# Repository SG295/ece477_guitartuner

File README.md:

# Automatic Guitar Tuner 🎸
☆ **Automatic Guitar Tuner Project for ECE477 (Senior Design) @ Purdue University** ☆

**Team Page: https://engineering.purdue.edu/477grp11/Team/team.html**

**Project Description:** Our automatic guitar tuner is a tool anyone can use by selecting the desired note and holding the tool against the tuning peg. A microphone will listen as the string is plucked by the user and make the proper adjustments thorugh a motor. An LCD screen will communicate when the guitar adjustments are finished being made. The design will also have other modes such as a free spin mode to allow the motor to assist in the restringing of a guitar.
Design parameters are:
  * A 3D printed case that holds all the components (PCB, battery, motor, etc.)
  * An STM32 microcontroller that controls all the components of the tuner (battery, motor, LCD screen, microphone)
  * A stepper motor connected to the microcontroller that rotates based on feedback from the microphone
  * A digital microphone that listens when prompted by the microcontroller. First, I2S is used to read the digital signal and then DSP is performed so that the microcontroller knows what frequency is being played.
  * A rechargable battery connected to a battery management system and the microcontroller. Powers all the components in the tuner.
  * A graphical LCD screen that is controlled by buttons on the tuner. It includes "Power", "^", ">", "<", and "v" buttons for the user to press to control the contents of the screen.

***

**For team members:**

Please make a branch for your respective part and title it according (i.e. if you're working on the motor, you can just title it "motor").

The command to create a branch (do this locally after you've pulled):
  * git checkout -b NEW_BRANCH_NAME

The commands (in order) to push your NEW branch: 
  * git add .
  * git commit -m "put message here"
  * git push origin -u NEW_BRANCH_NAME
   
**Once you have created and pushed the branch, you can push normally if you're on the branch. You can check this with "git branch".**

I have setup a platoform IO project here with basic settings with the STM32F407VG Discovery Boards we have at our table (looks like the image below). Make sure you're actually within the project folder (titled "PlatformIO-GuitarTuner") and not this repo when trying to upload code to the board. I'll list some documentation that will be useful below:
  * Reference Manual: https://www.st.com/resource/en/reference_manual/dm00031020-stm32f405-415-stm32f407-417-stm32f427-437-and-stm32f429-439-advanced-arm-based-32-bit-mcus-stmicroelectronics.pdf
  * STM32F407 Data Sheet: https://www.st.com/resource/en/datasheet/dm00037051.pdf

**DISCOVERY BOARD:**

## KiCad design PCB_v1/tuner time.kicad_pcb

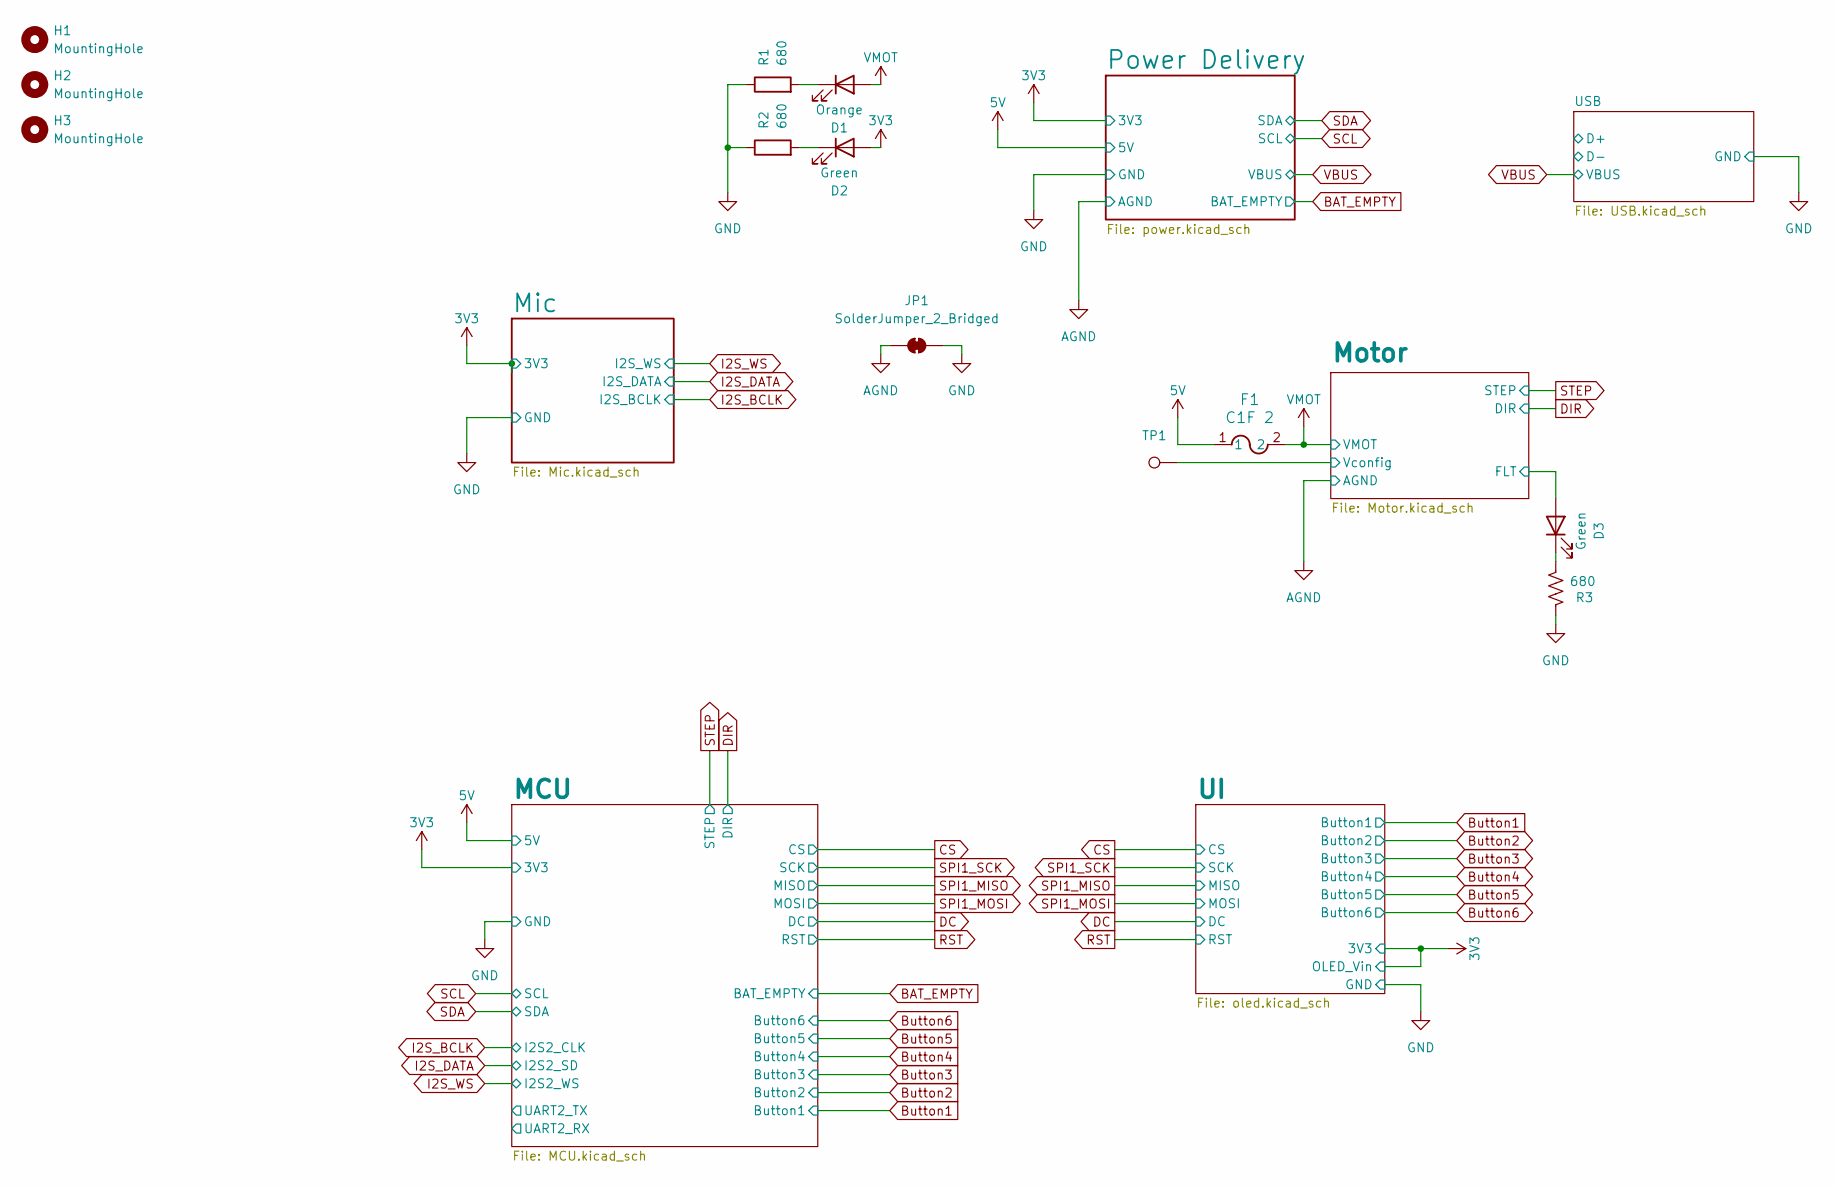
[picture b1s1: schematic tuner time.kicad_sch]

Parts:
D1: Orange; LED_0805_2012Metric_Pad1.15x1.40mm_HandSolder
D2, D3: Green; LED_0805_2012Metric_Pad1.15x1.40mm_HandSolder
F1: C1F 2; C1_BEL
H1, H2, H3: MountingHole; MountingHole_2.2mm_M2_DIN965_Pad_TopOnly
JP1: SolderJumper_2_Bridged; SolderJumper-2_P1.3mm_Bridged2Bar_RoundedPad1.0x1.5mm
R1, R2, R3: 680; R_0805_2012Metric
TP1: TestPoint_THTPad_D0.8mm_Drill0.4mm

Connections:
3V3: D2.2 (A); also elsewhere on the board
5V: F1.1; also elsewhere on the board
/Motor/FLT: D3.2 (A); also elsewhere on the board
/Motor/Vconfig: TP1.1; also elsewhere on the board
AGND: JP1.1 (A); also elsewhere on the board
GND: JP1.2 (B), R1.1, R2.1, R3.2; also elsewhere on the board
unnamed: D1.1 (K), R1.2
unnamed: D2.1 (K), R2.2
unnamed: D3.1 (K), R3.1
VMOT: D1.2 (A), F1.2; also elsewhere on the board

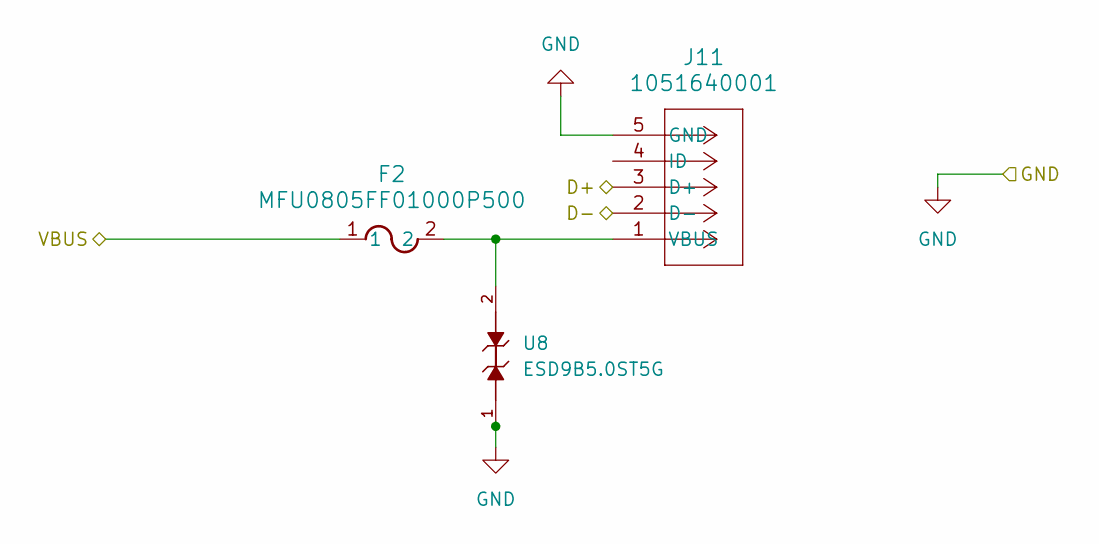
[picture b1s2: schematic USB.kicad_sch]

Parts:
F2: MFU0805FF01000P500; FUS_VISHAY_MFU0805_VIS
J11: 1051640001; CON00906_5_MOL
U8: ESD9B5.0ST5G; SODFL1006X40N

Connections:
GND: J11.5 (GND), U8.1; also elsewhere on the board
unnamed: F2.2, J11.1 (VBUS), U8.2
VBUS: F2.1; also elsewhere on the board

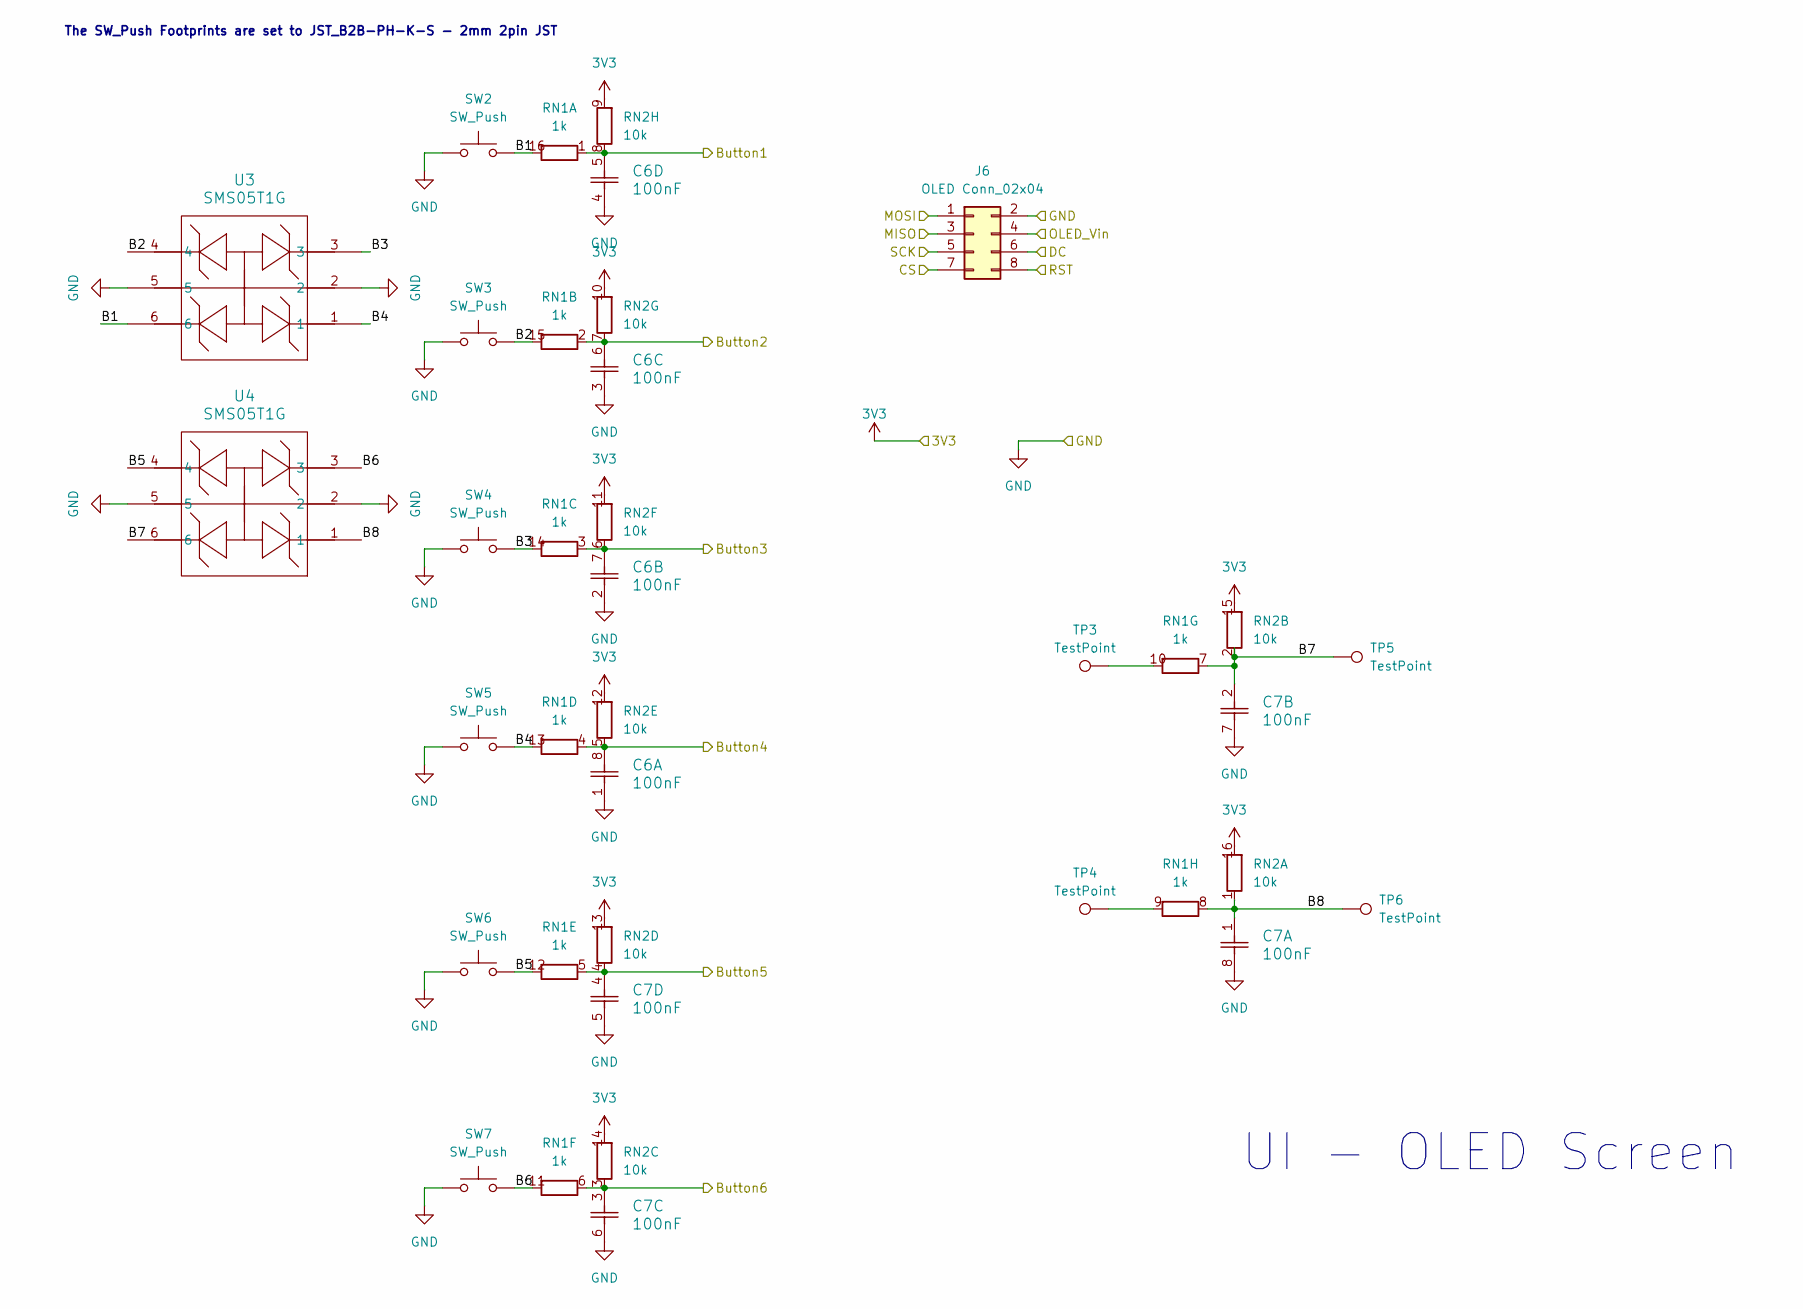
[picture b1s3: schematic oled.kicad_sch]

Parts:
C6, C7: 100nF; CAP_CA0612_3P2X1P6_YAG
J6: OLED Conn_02x04; PinHeader_2x04_P2.54mm_Vertical
RN1: 1k; RESCAXE50P280X160X55-16N
RN2: 10k; RESCAXE50P280X160X55-16N
SW2, SW3, SW4, SW5, SW6, SW7: SW_Push; JST_B2B-PH-K-S
TP3, TP4, TP5, TP6: TestPoint; TestPoint_THTPad_D0.8mm_Drill0.4mm
U3, U4: SMS05T1G; SOIC_05T1G_ONS

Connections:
3V3: J6.4, RN2.9 (R8.2), RN2.10 (R7.2), RN2.11 (R6.2), RN2.12 (R5.2), RN2.13 (R4.2), RN2.14 (R3.2), RN2.15 (R2.2), RN2.16 (R1.2); also elsewhere on the board
/UI/B1: RN1.16 (R1.2), SW2.2, U3.6
/UI/B2: RN1.15 (R2.2), SW3.2, U3.4
/UI/B3: RN1.14 (R3.2), SW4.2, U3.3
/UI/B4: RN1.13 (R4.2), SW5.2, U3.1
/UI/B5: RN1.12 (R5.2), SW6.2, U4.4
/UI/B6: RN1.11 (R6.2), SW7.2, U4.3
/UI/B7: C7.2, RN1.7 (R7.1), RN2.2 (R2.1), TP5.1, U4.6
/UI/B8: C7.1, RN1.8 (R8.1), RN2.1 (R1.1), TP6.1, U4.1
Button1: C6.5, RN1.1 (R1.1), RN2.8 (R8.1); also elsewhere on the board
Button2: C6.6, RN1.2 (R2.1), RN2.7 (R7.1); also elsewhere on the board
Button3: C6.7, RN1.3 (R3.1), RN2.6 (R6.1); also elsewhere on the board
Button4: C6.8, RN1.4 (R4.1), RN2.5 (R5.1); also elsewhere on the board
Button5: C7.4, RN1.5 (R5.1), RN2.4 (R4.1); also elsewhere on the board
Button6: C7.3, RN1.6 (R6.1), RN2.3 (R3.1); also elsewhere on the board
CS: J6.8; also elsewhere on the board
DC: J6.6; also elsewhere on the board
GND: C6.1, C6.2, C6.3, C6.4, C7.5, C7.6, C7.7, C7.8, J6.2, SW2.1, SW3.1, SW4.1, SW5.1, SW6.1, SW7.1, U3.2, U3.5, U4.2, U4.5; also elsewhere on the board
unnamed: RN1.10 (R7.2), TP3.1
unnamed: RN1.9 (R8.2), TP4.1
RST: J6.7; also elsewhere on the board
SPI1_MISO: J6.3; also elsewhere on the board
SPI1_MOSI: J6.1; also elsewhere on the board
SPI1_SCK: J6.5; also elsewhere on the board

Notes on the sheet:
The SW_Push Footprints are set to JST_B2B-PH-K-S - 2mm 2pin JST
UI - OLED Screen

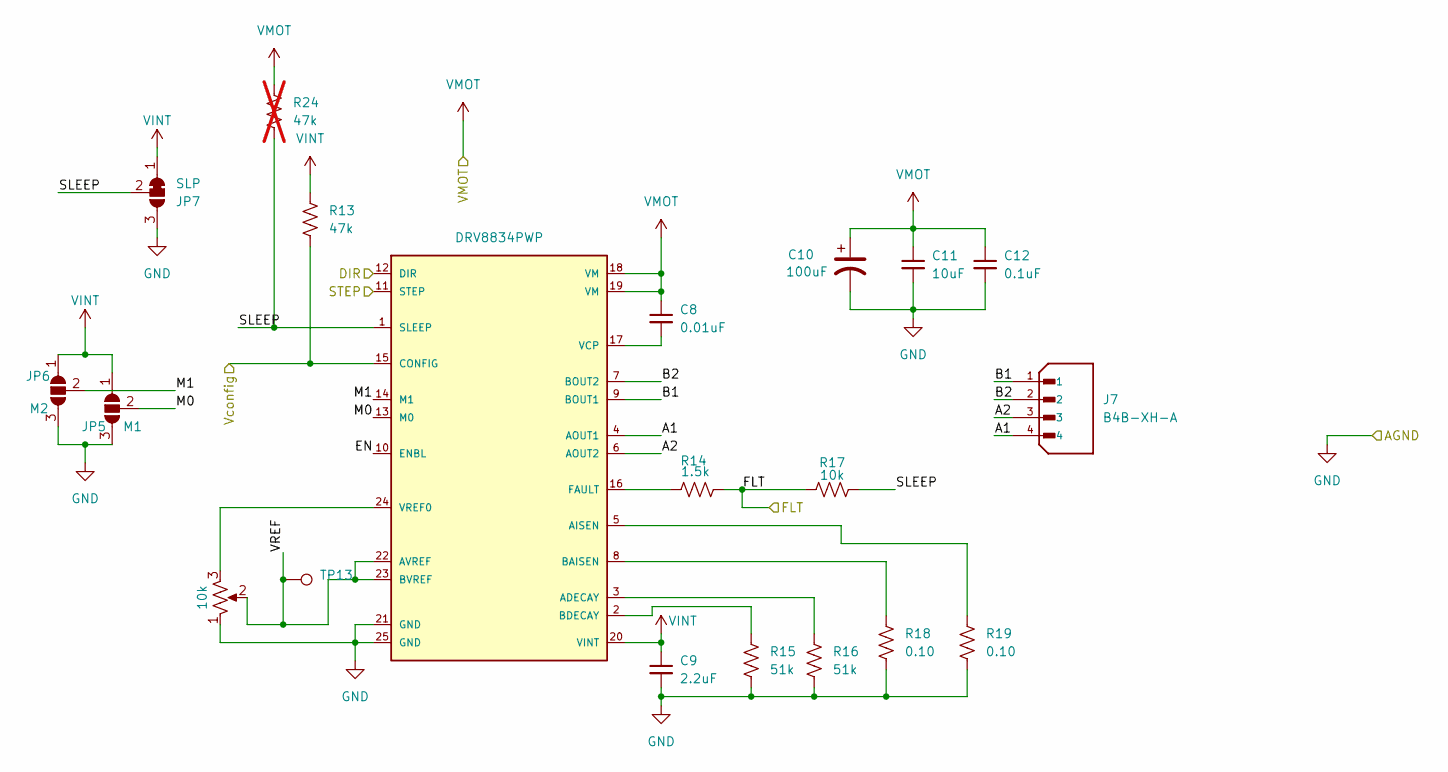
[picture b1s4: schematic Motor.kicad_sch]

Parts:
C8: 0.01uF; C_0805_2012Metric
C9: 2.2uF; C_0805_2012Metric
C10: 100uF; CAP_EEE1AA101WR
C11: 10uF; C_0805_2012Metric
C12: 0.1uF; C_0805_2012Metric
J7: B4B-XH-A; JST_B4B-XH-A; PARTREV 7/4/21
JP5: M1; SolderJumper-3_P1.3mm_Open_RoundedPad1.0x1.5mm
JP6: M2; SolderJumper-3_P1.3mm_Open_RoundedPad1.0x1.5mm
JP7: SLP; SolderJumper-3_P1.3mm_Bridged12_RoundedPad1.0x1.5mm
R13: 47k; R_0805_2012Metric
R14: 1.5k; R_0805_2012Metric
R15, R16: 51k; R_0805_2012Metric
R17: 10k; R_0805_2012Metric
R18, R19: 0.10; R_0805_2012Metric
R24: 47k; R_0805_2012Metric; not fitted
RV1: 10k; TRIM_TC33X-2-103E
TP13: TestPoint_THTPad_D0.8mm_Drill0.4mm
U5: DRV8834PWP; SOP65P640X120-25N

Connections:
/Motor/A1: J7.4, U5.4 (AOUT1)
/Motor/A2: J7.3, U5.6 (AOUT2)
/Motor/B1: J7.1, U5.9 (BOUT1)
/Motor/B2: J7.2, U5.7 (BOUT2)
/Motor/EN: U5.10 (ENBL)
/Motor/FLT: R14.2, R17.1; also elsewhere on the board
/Motor/M0: JP5.2 (C), U5.13 (M0)
/Motor/M1: JP6.2 (C), U5.14 (M1)
/Motor/SLEEP: JP7.2 (C), R17.2, R24.2, U5.1 (SLEEP)
/Motor/VREF: RV1.2, TP13.1, U5.22 (AVREF), U5.23 (BVREF)
/Motor/Vconfig: R13.2, U5.15 (CONFIG); also elsewhere on the board
AGND: C9.2, C10.2, C11.2, C12.2, JP5.3 (B), JP6.3 (B), JP7.3 (B), R15.2, R16.2, R18.2, R19.2, RV1.1, U5.21 (GND), U5.25 (GND); also elsewhere on the board
DIR: U5.12 (DIR); also elsewhere on the board
unnamed: R16.1, U5.3 (ADECAY)
unnamed: R19.1, U5.5 (AISEN)
unnamed: R18.1, U5.8 (BAISEN)
unnamed: R15.1, U5.2 (BDECAY)
unnamed: R14.1, U5.16 (FAULT)
unnamed: C8.2, U5.17 (VCP)
unnamed: RV1.3, U5.24 (VREF0)
STEP: U5.11 (STEP); also elsewhere on the board
VINT: C9.1, JP5.1 (A), JP6.1 (A), JP7.1 (A), R13.1, U5.20 (VINT)
VMOT: C8.1, C10.1, C11.1, C12.1, R24.1, U5.18 (VM), U5.19 (VM); also elsewhere on the board

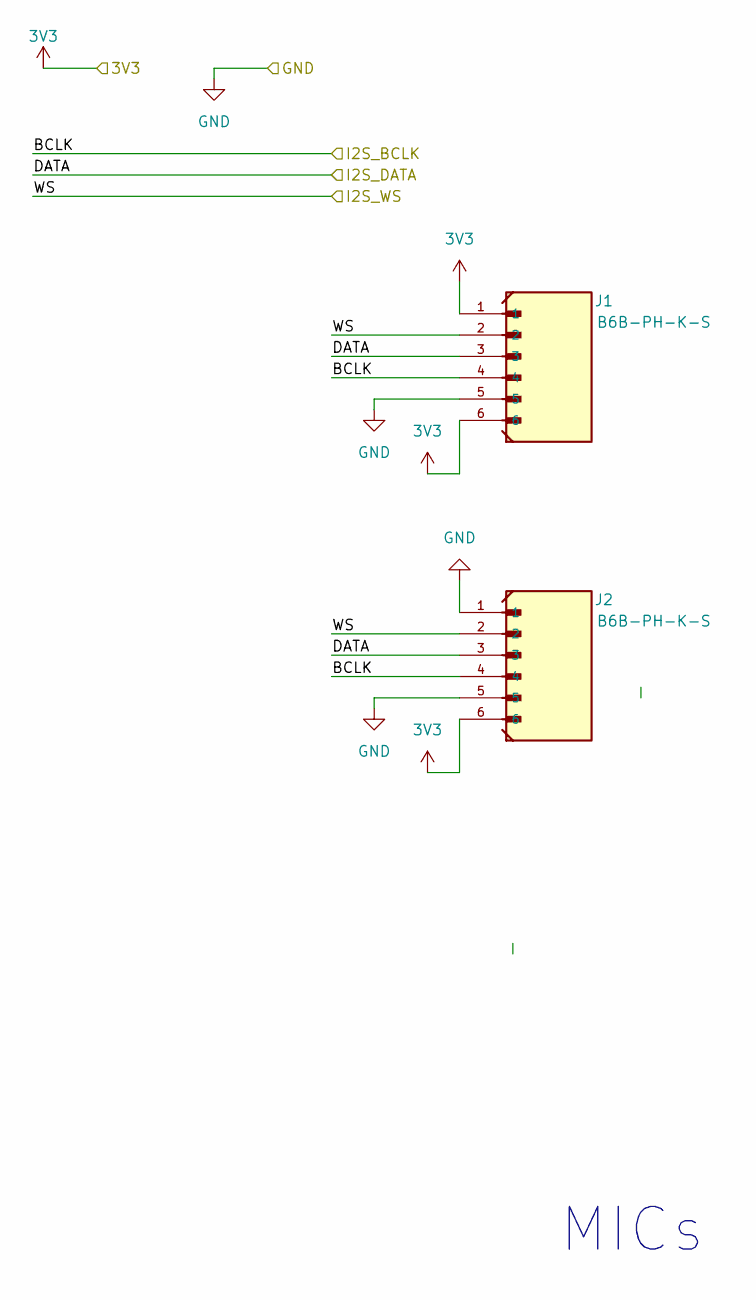
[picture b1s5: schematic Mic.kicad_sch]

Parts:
J1, J2: B6B-PH-K-S; JST_B6B-PH-K-S

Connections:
3V3: J1.1, J1.6, J2.6; also elsewhere on the board
GND: J1.5, J2.1, J2.5; also elsewhere on the board
I2S_BCLK: J1.4, J2.4; also elsewhere on the board
I2S_DATA: J1.3, J2.3; also elsewhere on the board
I2S_WS: J1.2, J2.2; also elsewhere on the board

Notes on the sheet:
MICs

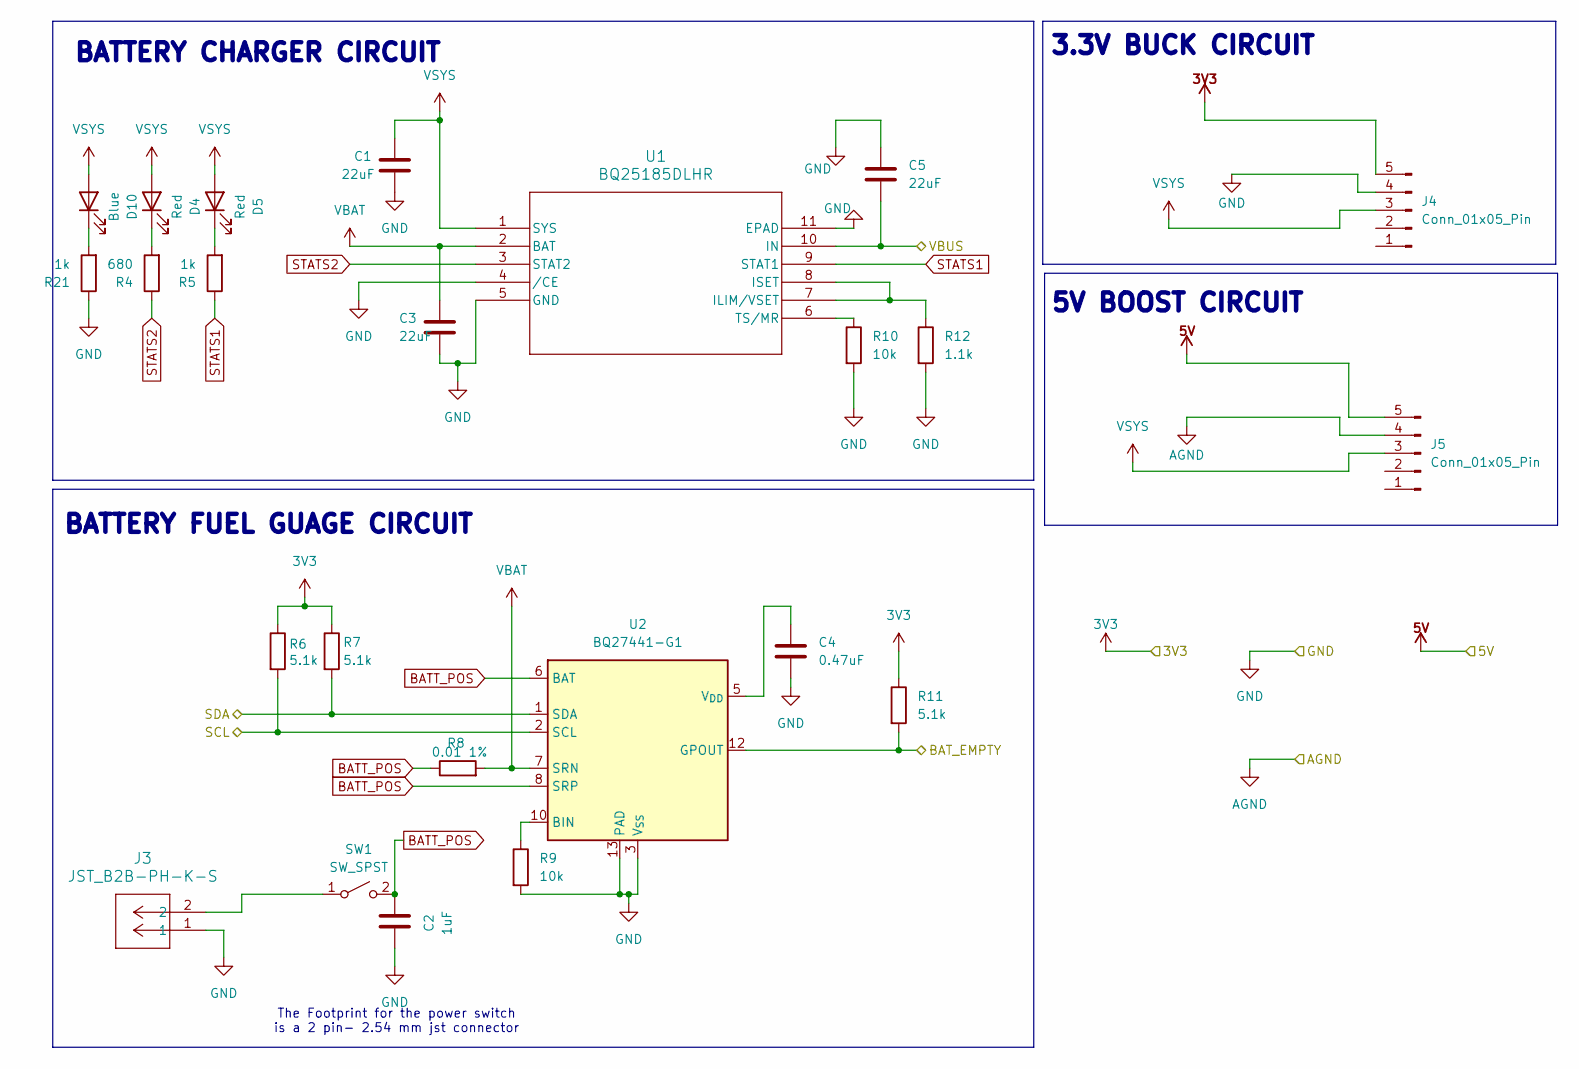
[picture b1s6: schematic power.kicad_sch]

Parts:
C1, C3, C5: 22uF; C_0805_2012Metric
C2: 1uF; C_0805_2012Metric
C4: 0.47uF; C_0805_2012Metric
D4, D5: Red; LED_0805_2012Metric_Pad1.15x1.40mm_HandSolder
D10: Blue; LED_0805_2012Metric_Pad1.15x1.40mm_HandSolder
J3: JST_B2B-PH-K-S
J4, J5: Conn_01x05_Pin; PinHeader_1x05_P2.54mm_Vertical
R4: 680; R_0805_2012Metric
R5, R21: 1k; R_0805_2012Metric
R6, R7, R11: 5.1k; R_0805_2012Metric
R8: 0.01 1%; R_0805_2012Metric
R9, R10: 10k; R_0805_2012Metric
R12: 1.1k; R_0805_2012Metric
SW1: SW_SPST; JST_B2B-PH-K-S
U1: BQ25185DLHR; WSON10_DLH_TEX
U2: BQ27441-G1; Texas_S-PDSO-N12

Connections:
3V3: J4.5, R6.1, R7.1, R11.1; also elsewhere on the board
5V: J5.5; also elsewhere on the board
AGND: J5.4; also elsewhere on the board
BATT_POS: C2.2, R8.1, SW1.2 (B), U2.6 (BAT), U2.8 (SRP)
BAT_EMPTY: R11.2, U2.12 (GPOUT); also elsewhere on the board
GND: C1.2, C2.1, C3.2, C4.2, C5.1, J3.1, J4.4, R9.2, R10.2, R12.2, R21.1, U1.4 (/CE), U1.5 (GND), U1.11 (EPAD), U2.3 (V_{SS}), U2.13 (PAD); also elsewhere on the board
unnamed: D4.1 (K), R4.2
unnamed: D5.1 (K), R5.2
unnamed: D10.1 (K), R21.2
unnamed: J3.2, SW1.1 (A)
unnamed: R12.1, U1.7 (ILIM/VSET), U1.8 (ISET)
unnamed: R10.1, U1.6 (TS/MR)
unnamed: R9.1, U2.10 (BIN)
unnamed: C4.1, U2.5 (V_{DD})
SCL: R6.2, U2.2 (SCL); also elsewhere on the board
SDA: R7.2, U2.1 (SDA); also elsewhere on the board
STATS1: R5.1, U1.9 (STAT1)
STATS2: R4.1, U1.3 (STAT2)
VBAT: C3.1, R8.2, U1.2 (BAT), U2.7 (SRN)
VBUS: C5.2, U1.10 (IN); also elsewhere on the board
VSYS: C1.1, D4.2 (A), D5.2 (A), D10.2 (A), J4.3, J5.3, U1.1 (SYS)

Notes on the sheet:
3.3V BUCK CIRCUIT
BATTERY CHARGER CIRCUIT
BATTERY FUEL GUAGE CIRCUIT
The Footprint for the power switch is a 2 pin- 2.54 mm jst connector
5V BOOST CIRCUIT

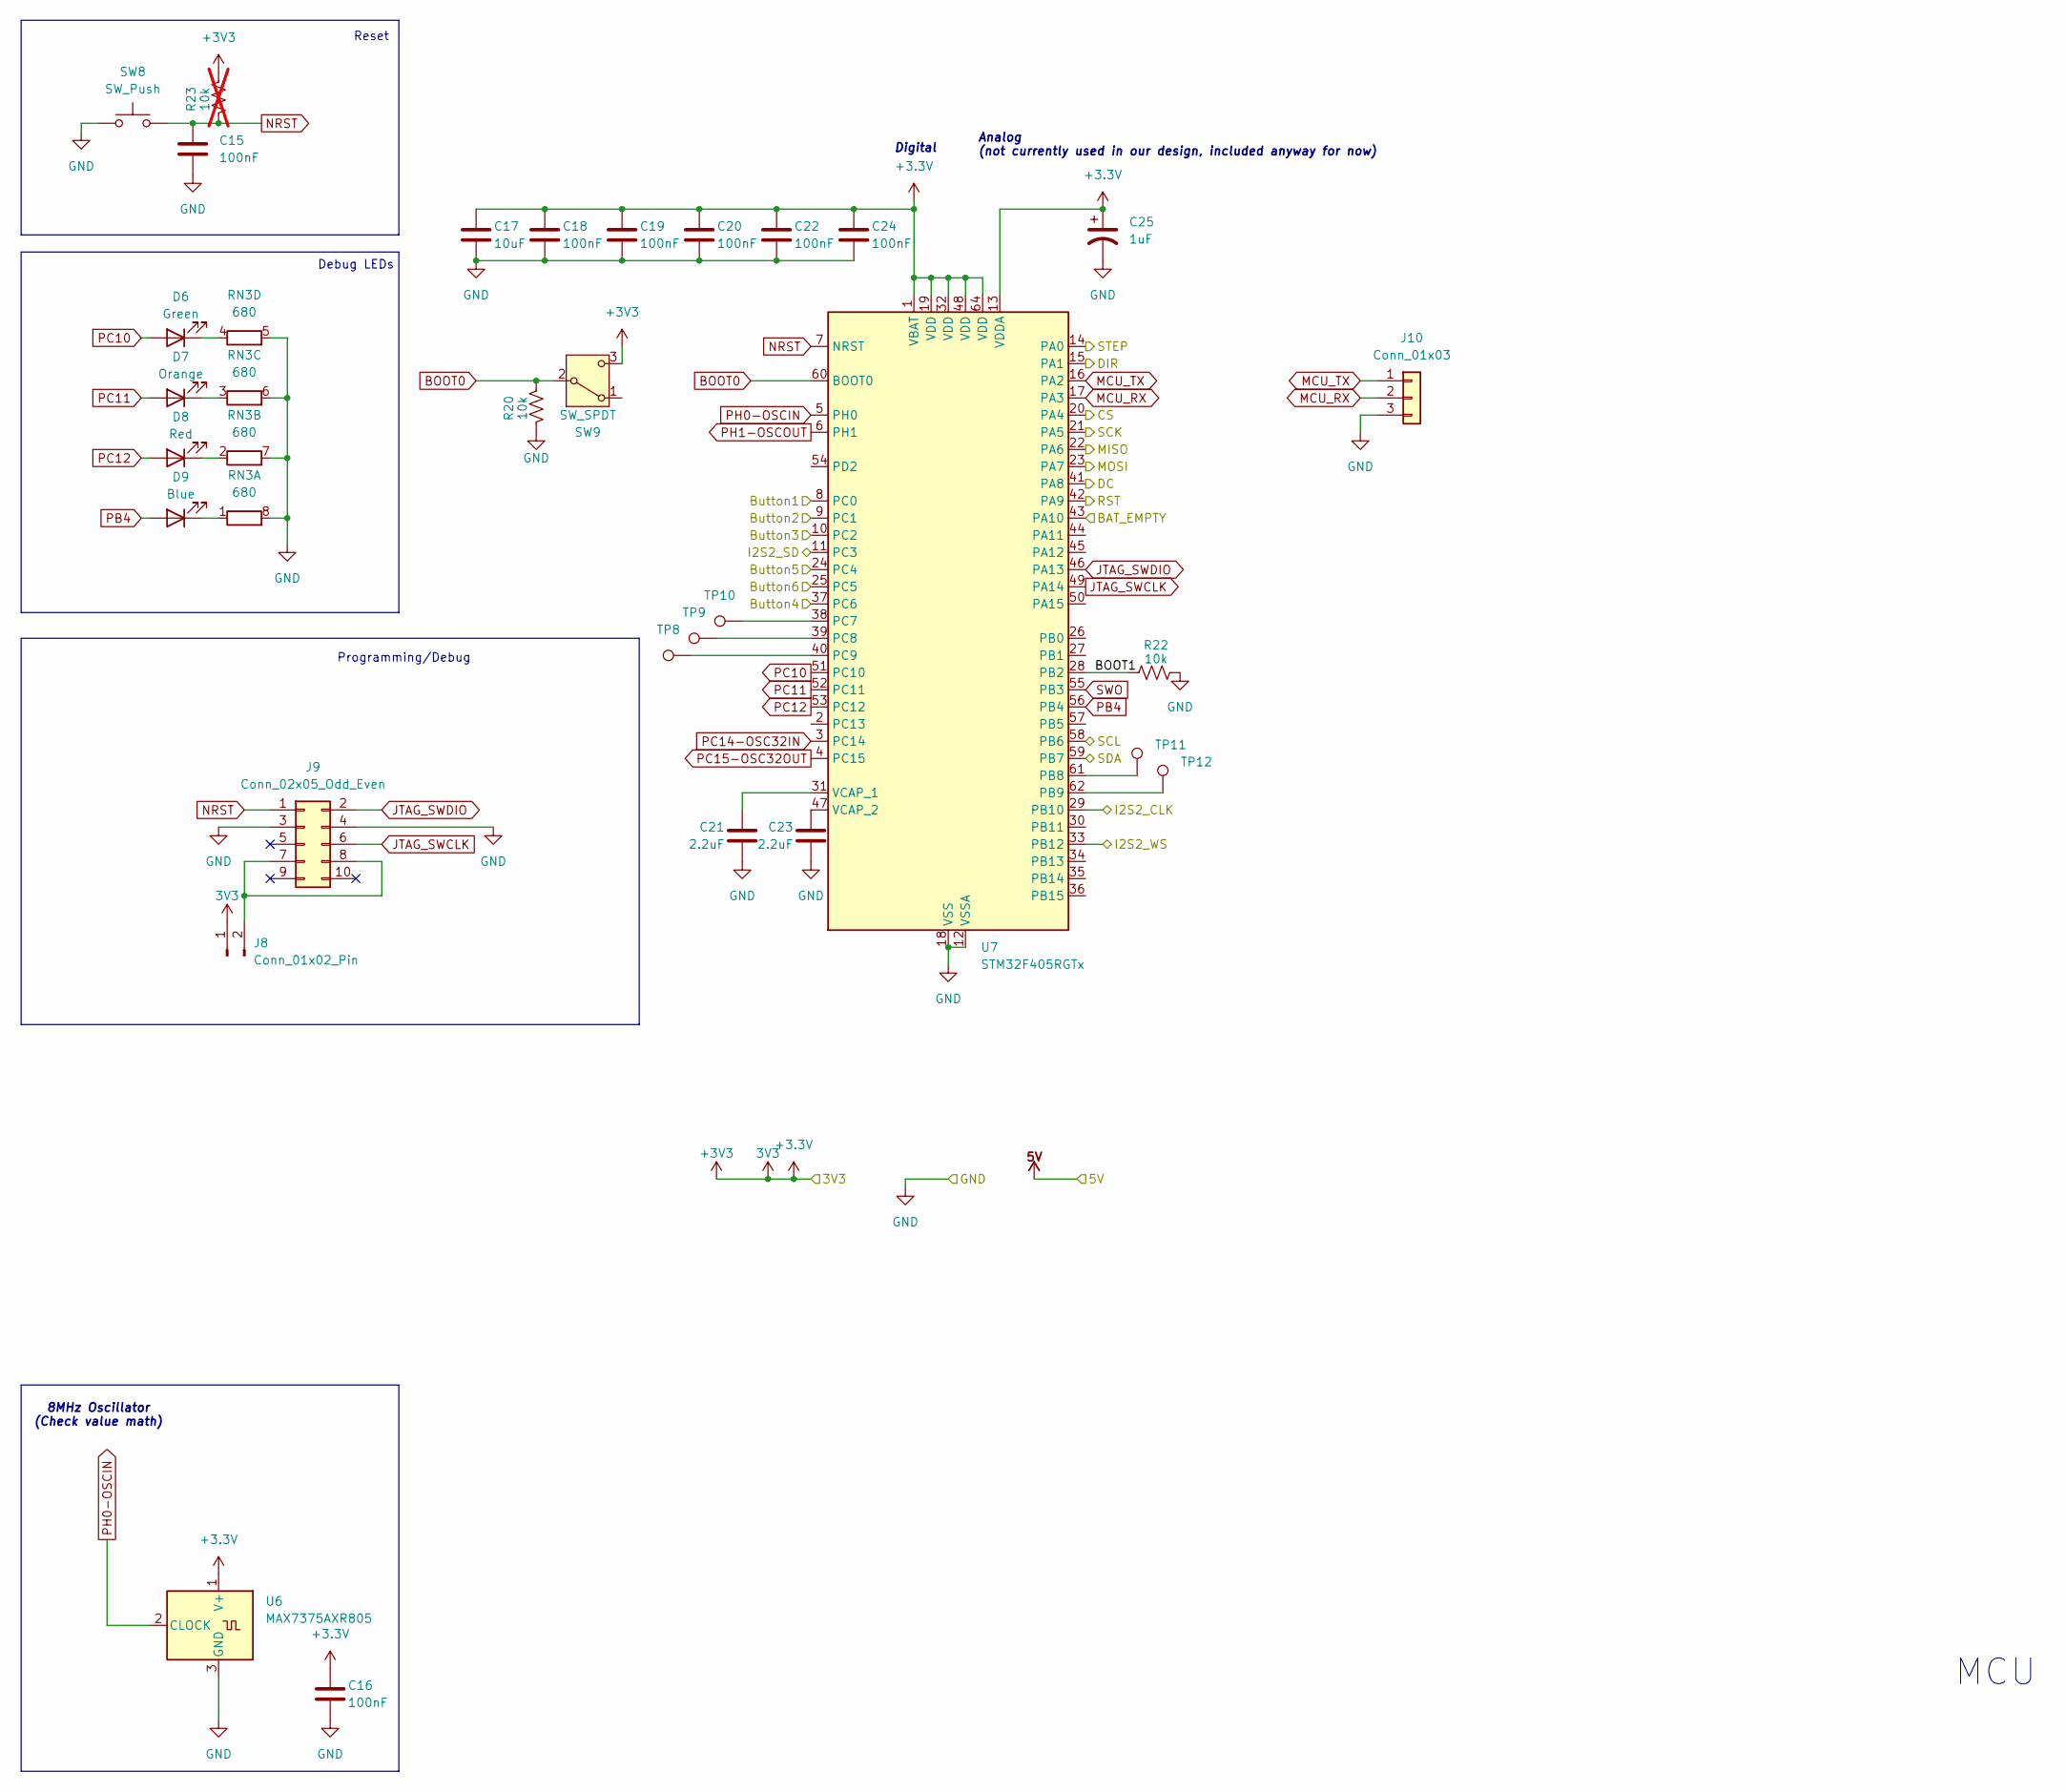
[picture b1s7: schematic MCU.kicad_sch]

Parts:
C15, C16, C18, C19, C20, C22, C24: 100nF; C_0805_2012Metric
C17: 10uF; C_0805_2012Metric
C21, C23: 2.2uF; C_0805_2012Metric
C25: 1uF; C_1206_3216Metric_Pad1.33x1.80mm_HandSolder
D6: Green; LED_0805_2012Metric_Pad1.15x1.40mm_HandSolder
D7: Orange; LED_0805_2012Metric_Pad1.15x1.40mm_HandSolder
D8: Red; LED_0805_2012Metric_Pad1.15x1.40mm_HandSolder
D9: Blue; LED_0805_2012Metric_Pad1.15x1.40mm_HandSolder
J8: Conn_01x02_Pin; PinHeader_1x02_P2.54mm_Vertical
J9: Conn_02x05_Odd_Even; IDC-Header_2x05_P2.54mm_Vertical
J10: Conn_01x03; PinHeader_1x03_P2.54mm_Vertical
R20, R22: 10k; R_0805_2012Metric
R23: 10k; R_0805_2012Metric; not fitted
RN3: 680; RESCAXS80P320X160X60-8N
SW8: SW_Push; SW_TS04-66-65-BK-160-SMT
SW9: SW_SPDT; SW_SPDT_PCM12
TP8, TP9, TP10, TP11, TP12: TestPoint_THTPad_D0.8mm_Drill0.4mm
U6: MAX7375AXR805; SOT-323_SC-70
U7: STM32F405RGTx; LQFP-64_10x10mm_P0.5mm

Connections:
3V3: C16.1, C17.1, C18.1, C19.1, C20.1, C22.1, C24.1, C25.1, J8.1, R23.1, SW9.3 (C), U6.1 (V+), U7.1 (VBAT), U7.13 (VDDA), U7.19 (VDD), U7.32 (VDD), U7.48 (VDD), U7.64 (VDD); also elsewhere on the board
/MCU/BOOT1: R22.1, U7.28 (PB2)
BAT_EMPTY: U7.43 (PA10); also elsewhere on the board
BOOT0: R20.1, SW9.2 (B), U7.60 (BOOT0)
Button1: U7.8 (PC0); also elsewhere on the board
Button2: U7.9 (PC1); also elsewhere on the board
Button3: U7.10 (PC2); also elsewhere on the board
Button4: U7.37 (PC6); also elsewhere on the board
Button5: U7.24 (PC4); also elsewhere on the board
Button6: U7.25 (PC5); also elsewhere on the board
CS: U7.20 (PA4); also elsewhere on the board
DC: U7.41 (PA8); also elsewhere on the board
DIR: U7.15 (PA1); also elsewhere on the board
GND: C15.2, C16.2, C17.2, C18.2, C19.2, C20.2, C21.2, C22.2, C23.2, C24.2, C25.2, J9.3, J9.4, J10.3, R20.2, R22.2, RN3.5 (R4.2), RN3.6 (R3.2), RN3.7 (R2.2), RN3.8 (R1.2), SW8.1, U6.3 (GND), U7.12 (VSSA), U7.18 (VSS), U7.63 (VSS); also elsewhere on the board
I2S_BCLK: U7.29 (PB10); also elsewhere on the board
I2S_DATA: U7.11 (PC3); also elsewhere on the board
I2S_WS: U7.33 (PB12); also elsewhere on the board
JTAG_SWCLK: J9.6, U7.49 (PA14)
JTAG_SWDIO: J9.2, U7.46 (PA13)
MCU_RX: J10.2, U7.17 (PA3)
MCU_TX: J10.1, U7.16 (PA2)
NRST: C15.1, J9.1, R23.2, SW8.2, U7.7 (NRST)
unnamed: D6.1 (K), RN3.4 (R4.1)
unnamed: D7.1 (K), RN3.3 (R3.1)
unnamed: D8.1 (K), RN3.2 (R2.1)
unnamed: D9.1 (K), RN3.1 (R1.1)
unnamed: J8.2, J9.7, J9.8
unnamed: TP11.1, U7.61 (PB8)
unnamed: TP12.1, U7.62 (PB9)
unnamed: TP10.1, U7.38 (PC7)
unnamed: TP9.1, U7.39 (PC8)
unnamed: TP8.1, U7.40 (PC9)
unnamed: C21.1, U7.31 (VCAP_1)
unnamed: C23.1, U7.47 (VCAP_2)
PB4: D9.2 (A), U7.56 (PB4)
PC10: D6.2 (A), U7.51 (PC10)
PC11: D7.2 (A), U7.52 (PC11)
PC12: D8.2 (A), U7.53 (PC12)
PC14-OSC32IN: U7.3 (PC14)
PC15-OSC32OUT: U7.4 (PC15)
PH0-OSCIN: U6.2 (CLOCK), U7.5 (PH0)
PH1-OSCOUT: U7.6 (PH1)
RST: U7.42 (PA9); also elsewhere on the board
SCL: U7.58 (PB6); also elsewhere on the board
SDA: U7.59 (PB7); also elsewhere on the board
SPI1_MISO: U7.22 (PA6); also elsewhere on the board
SPI1_MOSI: U7.23 (PA7); also elsewhere on the board
SPI1_SCK: U7.21 (PA5); also elsewhere on the board
STEP: U7.14 (PA0); also elsewhere on the board
SWO: U7.55 (PB3)

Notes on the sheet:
Digital
MCU
8MHz Oscillator (Check value math)
Analog (not currently used in our design, included anyway for now)
Programming/Debug
Debug LEDs
Reset
